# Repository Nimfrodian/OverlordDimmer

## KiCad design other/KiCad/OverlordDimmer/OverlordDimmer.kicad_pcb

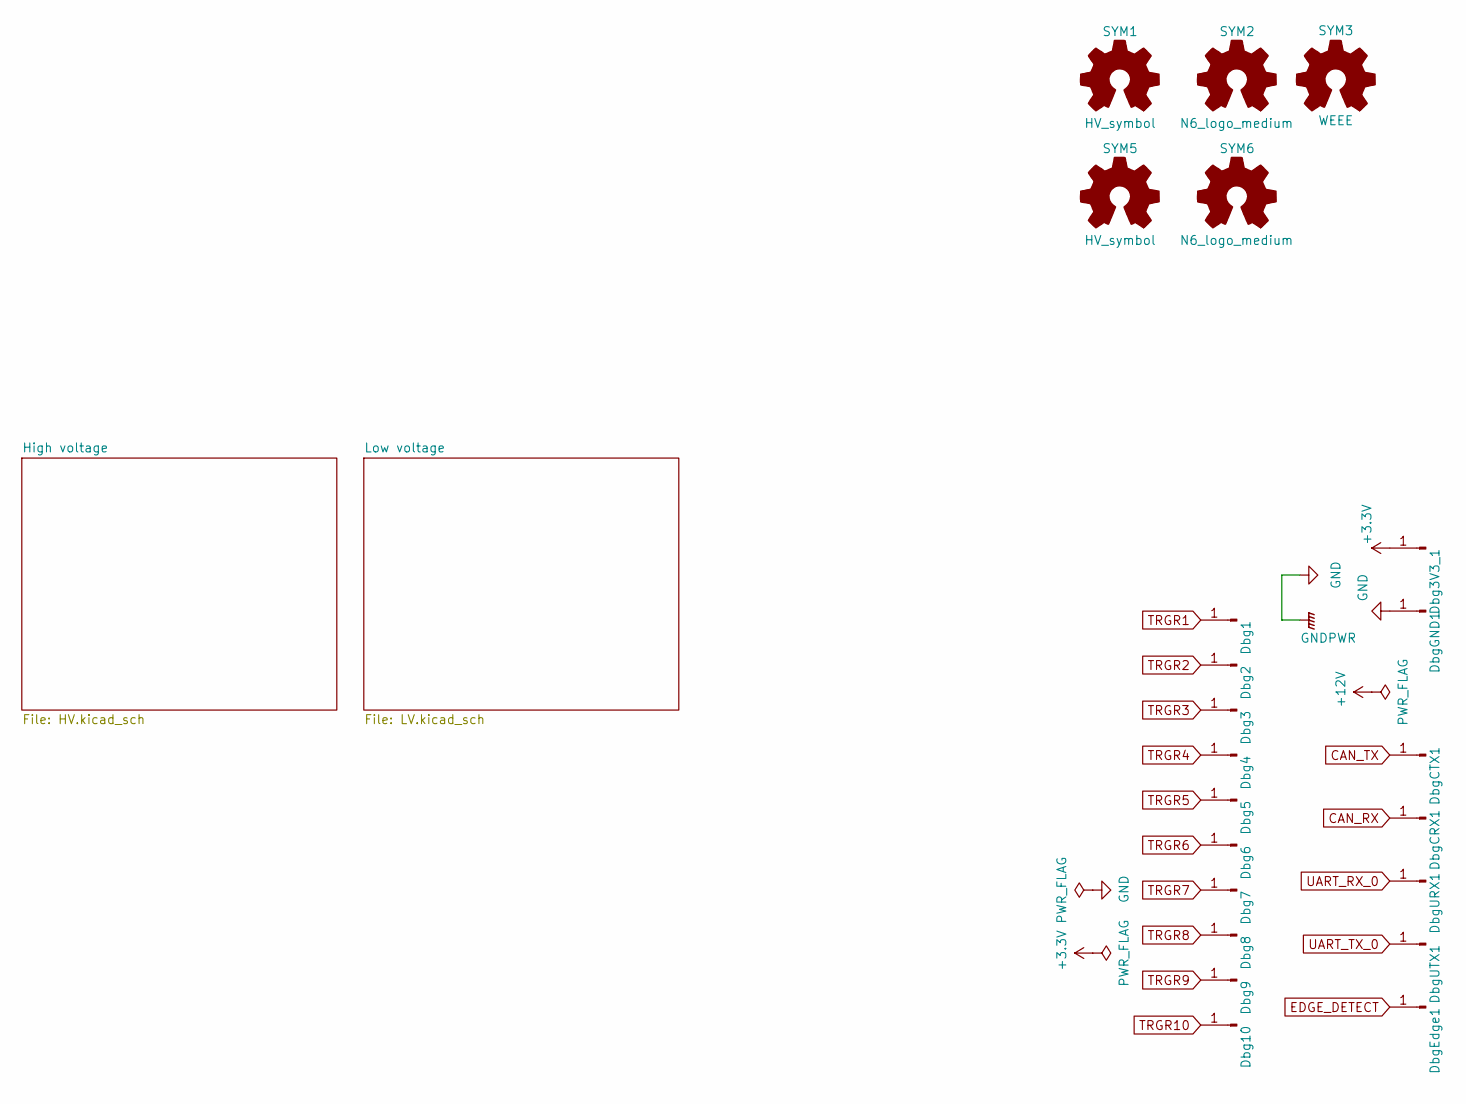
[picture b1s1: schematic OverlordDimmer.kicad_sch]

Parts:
Dbg1, Dbg2, Dbg3, Dbg3V3_1, Dbg4, Dbg5, Dbg6, Dbg7, Dbg8, Dbg9, Dbg10: Connector_Conn_01x01_Male; PinHeader_1x01_P2.54mm_Vertical
DbgCRX1: Connector_Conn_01x01_Male; PinHeader_1x01_P2.54mm_Vertical
DbgCTX1: Connector_Conn_01x01_Male; PinHeader_1x01_P2.54mm_Vertical
DbgEdge1: Connector_Conn_01x01_Male; PinHeader_1x01_P2.54mm_Vertical
DbgGND1: Connector_Conn_01x01_Male; PinHeader_1x01_P2.54mm_Vertical
DbgURX1: Connector_Conn_01x01_Male; PinHeader_1x01_P2.54mm_Vertical
DbgUTX1: Connector_Conn_01x01_Male; PinHeader_1x01_P2.54mm_Vertical
SYM1, SYM5: HV_symbol
SYM2, SYM6: N6_logo_medium; Symbol_N6Industries_medium
SYM3: WEEE; WEEE-Logo_5.6x8mm_SilkScreen

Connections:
+3.3V: Dbg3V3_1.1; also elsewhere on the board
CAN_RX: DbgCRX1.1; also elsewhere on the board
CAN_TX: DbgCTX1.1; also elsewhere on the board
EDGE_DETECT: DbgEdge1.1; also elsewhere on the board
GND: DbgGND1.1; also elsewhere on the board
TRGR1: Dbg1.1; also elsewhere on the board
TRGR2: Dbg2.1; also elsewhere on the board
TRGR3: Dbg3.1; also elsewhere on the board
TRGR4: Dbg4.1; also elsewhere on the board
TRGR5: Dbg5.1; also elsewhere on the board
TRGR6: Dbg6.1; also elsewhere on the board
TRGR7: Dbg7.1; also elsewhere on the board
TRGR8: Dbg8.1; also elsewhere on the board
TRGR9: Dbg9.1; also elsewhere on the board
TRGR10: Dbg10.1; also elsewhere on the board
UART_RX_0: DbgURX1.1; also elsewhere on the board
UART_TX_0: DbgUTX1.1; also elsewhere on the board

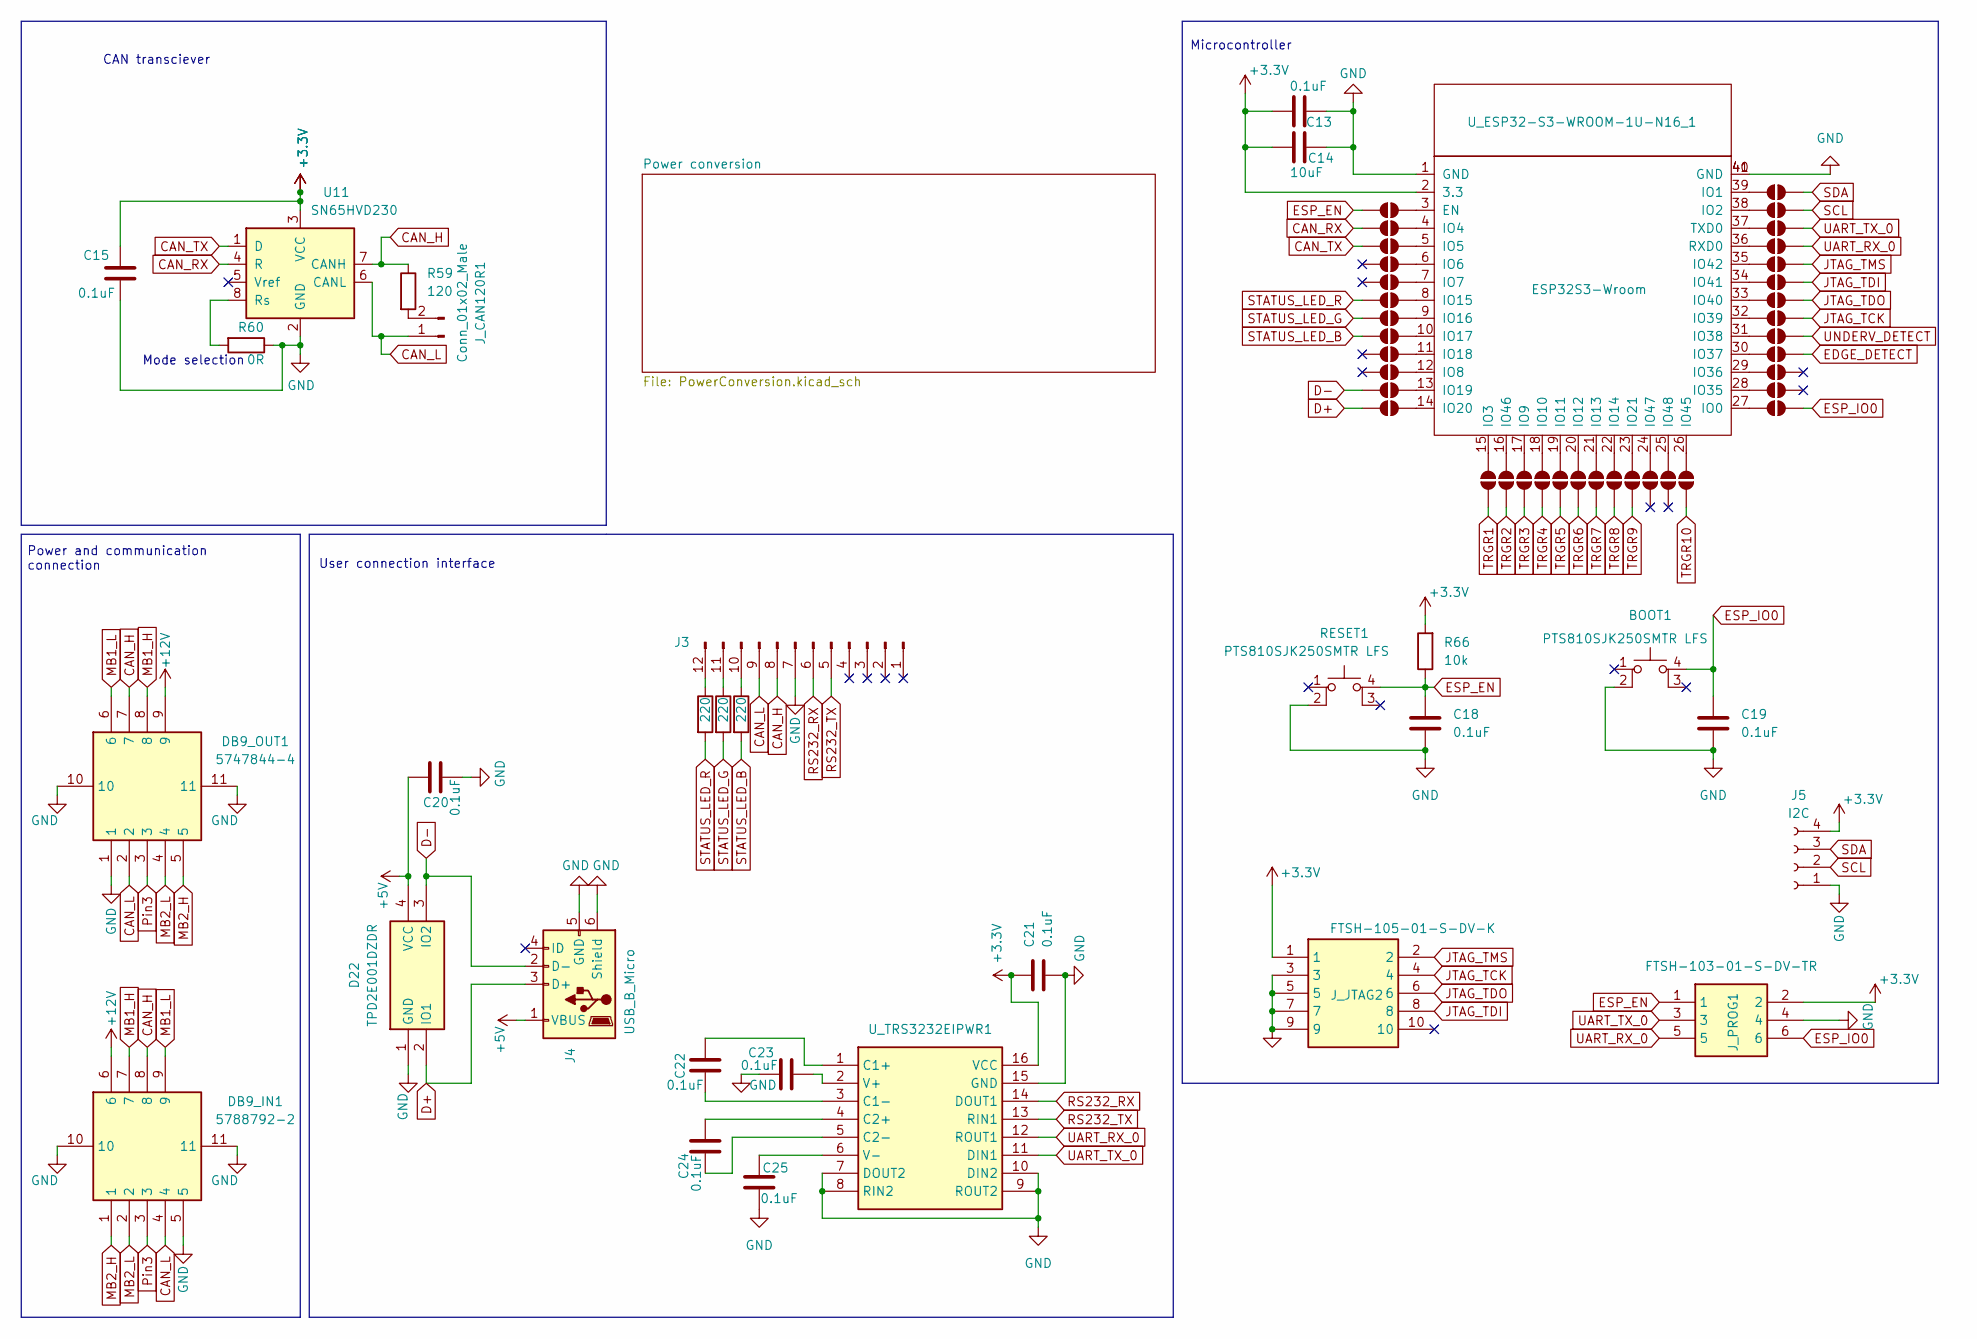
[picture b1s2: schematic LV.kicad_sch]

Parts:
BOOT1: PTS810SJK250SMTR LFS; PTS810SJK250SMTRLFS
C13, C15, C18, C19, C20, C21, C22, C23, C24, C25: 0.1uF; C_0805_2012Metric_Pad1.18x1.45mm_HandSolder
C14: 10uF; C_0805_2012Metric_Pad1.18x1.45mm_HandSolder
D22: TPD2E001DZDR; Mouser Part Number 595-TPD2E001DZDR
DB9_IN1: 5788792-2; 5788792; Mouser Part Number 571-5747844-4
DB9_OUT1: 5747844-4; 57478444; Mouser Part Number 571-5747844-4
J3: Conn_01x12_Pin; Molex_Picoflex_90325-0012_2x06_P1.27mm_Vertical
J4: USB_B_Micro; USB_Micro-B_Wuerth_614105150721_Vertical_CircularHoles
J5: I2C; PinHeader_1x04_P1.27mm_Vertical
JP1, JP2, JP3, JP4, JP5, JP6, JP7, JP8, JP9, JP10, JP11, JP12, JP13, JP14, JP15, JP16, JP17, JP18, JP19, JP20, JP21, JP22, JP23, JP24, JP25, JP26, JP27, JP28, JP29, JP30, JP31, JP32, JP33, JP34, JP35, JP36, JP37: SolderJumper_2_Open; SolderJumper-2_P1.3mm_Open_RoundedPad1.0x1.5mm
J_CAN120R1: Conn_01x02_Male; PinHeader_1x02_P2.54mm_Vertical
J_JTAG2: FTSH-105-01-S-DV-K; FTSH-105-XX-YYY-DV-K; Mouser Part Number 200-FTSH10501SDVK
J_PROG1: FTSH-103-01-S-DV-TR; FTSH-103-XX-YYY-DV-TR; Mouser Part Number 200-FTSH10301SDVTR
R59: 120; R_0805_2012Metric_Pad1.20x1.40mm_HandSolder
R60: 0R; R_0805_2012Metric_Pad1.20x1.40mm_HandSolder
R63, R64, R65: 220; R_0805_2012Metric_Pad1.20x1.40mm_HandSolder
R66: 10k; R_0805_2012Metric_Pad1.20x1.40mm_HandSolder
RESET1: PTS810SJK250SMTR LFS; PTS810SJK250SMTRLFS
U11: SN65HVD230; SOIC-8_3.9x4.9mm_P1.27mm
U_ESP32-S3-WROOM-1U-N16_1: ESP32S3-Wroom; ESP32-S3-WROOM-1U
U_TRS3232EIPWR1: TRS3232EIPWR; SOP65P640X120-16N; Mouser Part Number 595-TRS3232EIPWR

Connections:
+3.3V: C13.1, C14.1, C15.1, C21.1, J5.4, J_JTAG2.1, J_PROG1.2, R66.2, U11.3 (VCC), U_ESP32-S3-WROOM-1U-N16_1.2 (3.3), U_TRS3232EIPWR1.16 (VCC); also elsewhere on the board
+5V: C20.1, D22.4 (VCC), J4.1 (VBUS); also elsewhere on the board
+12V: DB9_IN1.6, DB9_OUT1.9; also elsewhere on the board
CAN_H: DB9_IN1.8, DB9_OUT1.7, J3.8, R59.1, U11.7 (CANH)
CAN_L: DB9_IN1.4, DB9_OUT1.2, J3.9, J_CAN120R1.1, U11.6 (CANL)
CAN_RX: JP4.2 (B), U11.4 (R); also elsewhere on the board
CAN_TX: JP6.2 (B), U11.1 (D); also elsewhere on the board
D+: D22.2 (IO1), J4.3 (D+), JP24.2 (B)
D-: D22.3 (IO2), J4.2 (D-), JP22.2 (B)
EDGE_DETECT: JP19.2 (B); also elsewhere on the board
ESP_EN: C18.1, JP2.2 (B), J_PROG1.1, R66.1, RESET1.4 (A)
ESP_IO0: BOOT1.4 (A), C19.1, JP25.2 (B), J_PROG1.6
GND: BOOT1.2, C13.2, C14.2, C15.2, C18.2, C19.2, C20.2, C21.2, C23.1, C25.1, D22.1 (GND), DB9_IN1.5, DB9_IN1.10, DB9_IN1.11, DB9_OUT1.1, DB9_OUT1.10, DB9_OUT1.11, J3.7, J4.5 (GND), J4.6 (Shield), J5.1, J_JTAG2.3, J_JTAG2.5, J_JTAG2.7, J_JTAG2.9, J_PROG1.4, R60.1, RESET1.2, U11.2 (GND), U_ESP32-S3-WROOM-1U-N16_1.1 (GND), U_ESP32-S3-WROOM-1U-N16_1.40 (GND), U_ESP32-S3-WROOM-1U-N16_1.41 (GND), U_TRS3232EIPWR1.7 (DOUT2), U_TRS3232EIPWR1.8 (RIN2), U_TRS3232EIPWR1.9 (ROUT2), U_TRS3232EIPWR1.10 (DIN2), U_TRS3232EIPWR1.15 (GND); also elsewhere on the board
JTAG_TCK: JP15.2 (B), J_JTAG2.4
JTAG_TDI: JP11.2 (B), J_JTAG2.8
JTAG_TDO: JP13.2 (B), J_JTAG2.6
JTAG_TMS: JP9.2 (B), J_JTAG2.2
MB1_H: DB9_IN1.7, DB9_OUT1.8
MB1_L: DB9_IN1.9, DB9_OUT1.6
MB2_H: DB9_IN1.1, DB9_OUT1.5
MB2_L: DB9_IN1.2, DB9_OUT1.4
unnamed: J3.10, R65.1
unnamed: J3.11, R64.1
unnamed: J3.12, R63.1
unnamed: JP1.1 (A), U_ESP32-S3-WROOM-1U-N16_1.39 (IO1)
unnamed: JP2.1 (A), U_ESP32-S3-WROOM-1U-N16_1.3 (EN)
unnamed: JP3.1 (A), U_ESP32-S3-WROOM-1U-N16_1.38 (IO2)
unnamed: JP4.1 (A), U_ESP32-S3-WROOM-1U-N16_1.4 (IO4)
unnamed: JP5.1 (A), U_ESP32-S3-WROOM-1U-N16_1.37 (TXD0)
unnamed: JP6.1 (A), U_ESP32-S3-WROOM-1U-N16_1.5 (IO5)
unnamed: JP7.1 (A), U_ESP32-S3-WROOM-1U-N16_1.36 (RXD0)
unnamed: JP8.1 (A), U_ESP32-S3-WROOM-1U-N16_1.6 (IO6)
unnamed: JP9.1 (A), U_ESP32-S3-WROOM-1U-N16_1.35 (IO42)
unnamed: JP10.1 (A), U_ESP32-S3-WROOM-1U-N16_1.7 (IO7)
unnamed: JP11.1 (A), U_ESP32-S3-WROOM-1U-N16_1.34 (IO41)
unnamed: JP12.1 (A), U_ESP32-S3-WROOM-1U-N16_1.8 (IO15)
unnamed: JP13.1 (A), U_ESP32-S3-WROOM-1U-N16_1.33 (IO40)
unnamed: JP14.1 (A), U_ESP32-S3-WROOM-1U-N16_1.9 (IO16)
unnamed: JP15.1 (A), U_ESP32-S3-WROOM-1U-N16_1.32 (IO39)
unnamed: JP16.1 (A), U_ESP32-S3-WROOM-1U-N16_1.10 (IO17)
unnamed: JP17.1 (A), U_ESP32-S3-WROOM-1U-N16_1.31 (IO38)
unnamed: JP18.1 (A), U_ESP32-S3-WROOM-1U-N16_1.11 (IO18)
unnamed: JP19.1 (A), U_ESP32-S3-WROOM-1U-N16_1.30 (IO37)
unnamed: JP20.1 (A), U_ESP32-S3-WROOM-1U-N16_1.12 (IO8)
unnamed: JP21.1 (A), U_ESP32-S3-WROOM-1U-N16_1.29 (IO36)
unnamed: JP22.1 (A), U_ESP32-S3-WROOM-1U-N16_1.13 (IO19)
unnamed: JP23.1 (A), U_ESP32-S3-WROOM-1U-N16_1.28 (IO35)
unnamed: JP24.1 (A), U_ESP32-S3-WROOM-1U-N16_1.14 (IO20)
unnamed: JP25.1 (A), U_ESP32-S3-WROOM-1U-N16_1.27 (IO0)
unnamed: JP26.1 (A), U_ESP32-S3-WROOM-1U-N16_1.15 (IO3)
unnamed: JP27.1 (A), U_ESP32-S3-WROOM-1U-N16_1.16 (IO46)
unnamed: JP28.1 (A), U_ESP32-S3-WROOM-1U-N16_1.17 (IO9)
unnamed: JP29.1 (A), U_ESP32-S3-WROOM-1U-N16_1.18 (IO10)
unnamed: JP30.1 (A), U_ESP32-S3-WROOM-1U-N16_1.19 (IO11)
unnamed: JP31.1 (A), U_ESP32-S3-WROOM-1U-N16_1.20 (IO12)
unnamed: JP32.1 (A), U_ESP32-S3-WROOM-1U-N16_1.21 (IO13)
unnamed: JP33.1 (A), U_ESP32-S3-WROOM-1U-N16_1.22 (IO14)
unnamed: JP34.1 (A), U_ESP32-S3-WROOM-1U-N16_1.23 (IO21)
unnamed: JP35.1 (A), U_ESP32-S3-WROOM-1U-N16_1.24 (IO47)
unnamed: JP36.1 (A), U_ESP32-S3-WROOM-1U-N16_1.25 (IO48)
unnamed: JP37.1 (A), U_ESP32-S3-WROOM-1U-N16_1.26 (IO45)
unnamed: J_CAN120R1.2, R59.2
unnamed: R60.2, U11.8 (Rs)
unnamed: C22.1, U_TRS3232EIPWR1.1 (C1+)
unnamed: C22.2, U_TRS3232EIPWR1.3 (C1-)
unnamed: C24.2, U_TRS3232EIPWR1.4 (C2+)
unnamed: C24.1, U_TRS3232EIPWR1.5 (C2-)
unnamed: C23.2, U_TRS3232EIPWR1.2 (V+)
unnamed: C25.2, U_TRS3232EIPWR1.6 (V-)
Pin3: DB9_IN1.3, DB9_OUT1.3
RS232_RX: J3.6, U_TRS3232EIPWR1.14 (DOUT1)
RS232_TX: J3.5, U_TRS3232EIPWR1.13 (RIN1)
SCL: J5.2, JP3.2 (B); also elsewhere on the board
SDA: J5.3, JP1.2 (B); also elsewhere on the board
STATUS_LED_B: JP16.2 (B), R65.2
STATUS_LED_G: JP14.2 (B), R64.2
STATUS_LED_R: JP12.2 (B), R63.2
TRGR1: JP26.2 (B); also elsewhere on the board
TRGR2: JP27.2 (B); also elsewhere on the board
TRGR3: JP28.2 (B); also elsewhere on the board
TRGR4: JP29.2 (B); also elsewhere on the board
TRGR5: JP30.2 (B); also elsewhere on the board
TRGR6: JP31.2 (B); also elsewhere on the board
TRGR7: JP32.2 (B); also elsewhere on the board
TRGR8: JP33.2 (B); also elsewhere on the board
TRGR9: JP34.2 (B); also elsewhere on the board
TRGR10: JP37.2 (B); also elsewhere on the board
UART_RX_0: JP7.2 (B), J_PROG1.5, U_TRS3232EIPWR1.12 (ROUT1); also elsewhere on the board
UART_TX_0: JP5.2 (B), J_PROG1.3, U_TRS3232EIPWR1.11 (DIN1); also elsewhere on the board
UNDERV_DETECT: JP17.2 (B); also elsewhere on the board

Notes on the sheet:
Power and communication connection
Microcontroller
Mode selection
CAN transciever
User connection interface

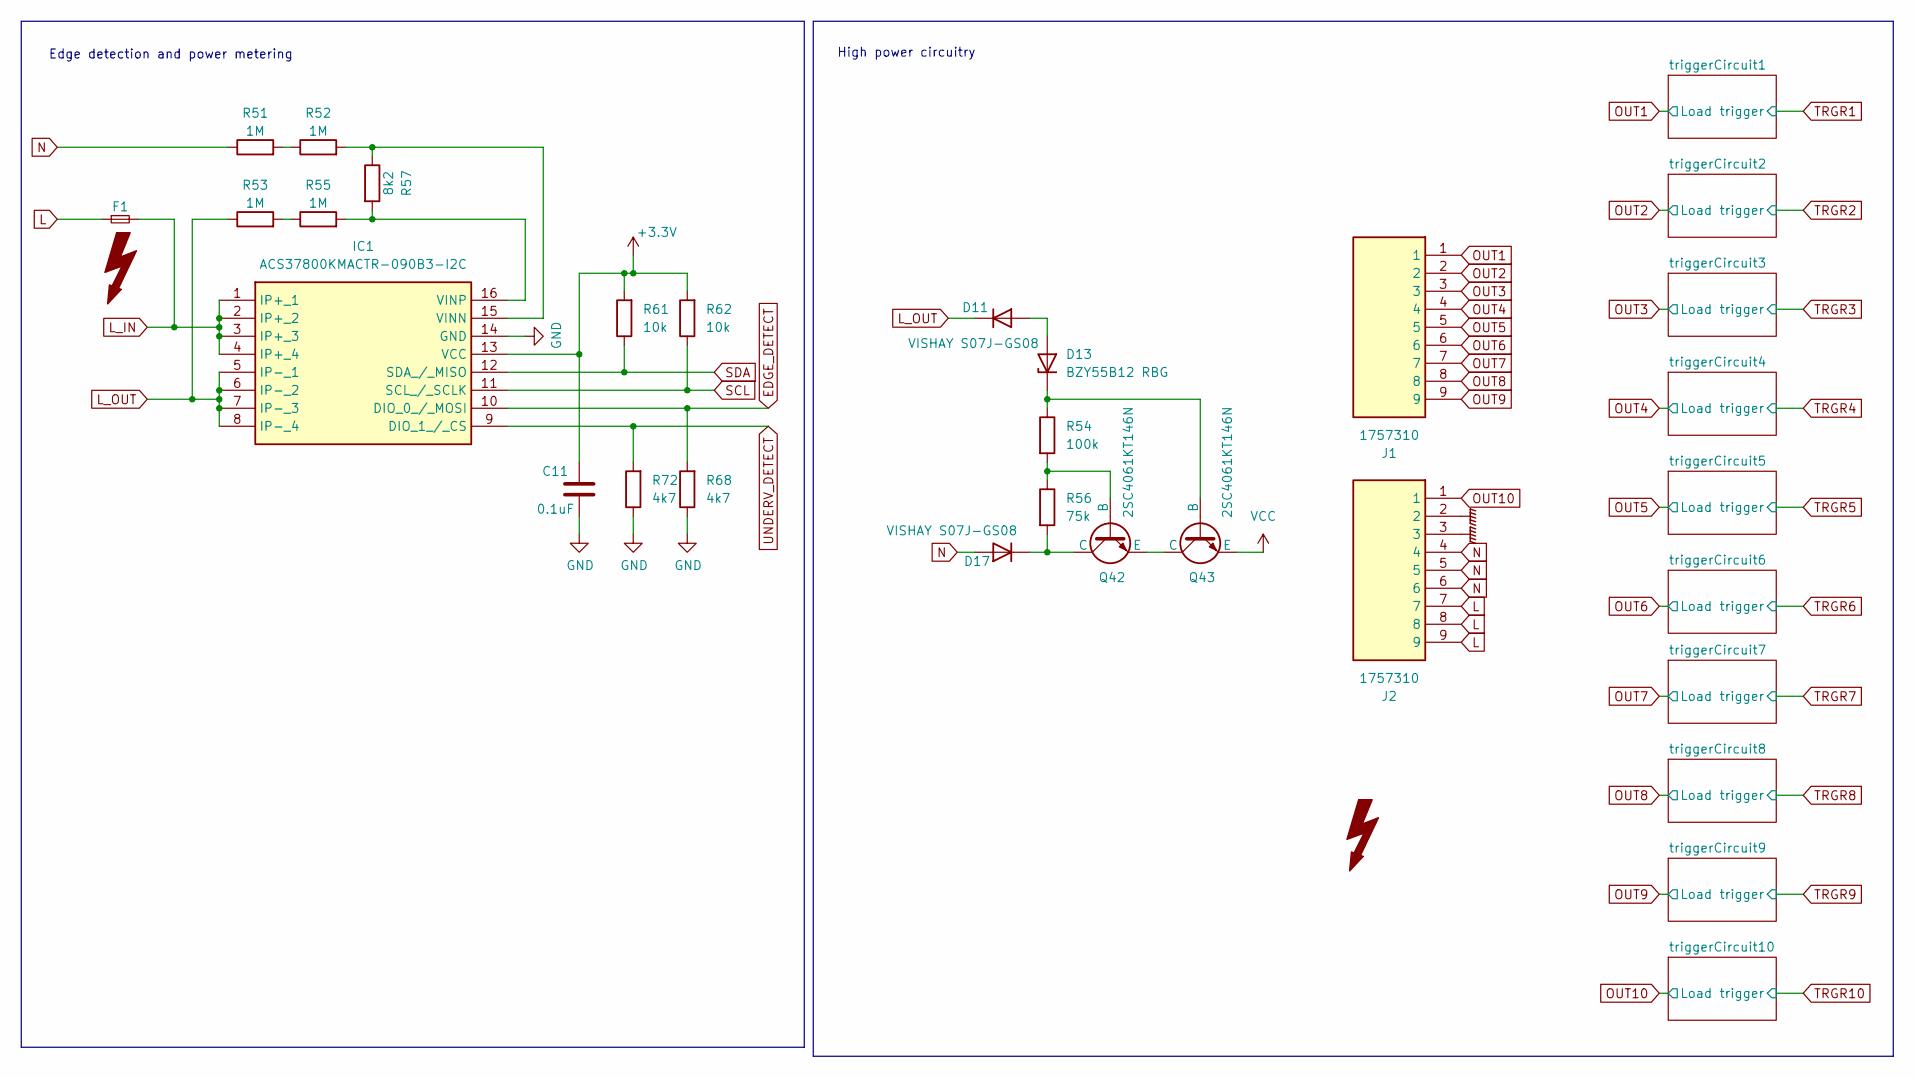
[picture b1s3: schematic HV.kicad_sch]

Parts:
C11: 0.1uF; C_0805_2012Metric_Pad1.18x1.45mm_HandSolder
D11, D17: VISHAY S07J-GS08; D_SMF
D13: BZY55B12 RBG; D_0805_2012Metric_Pad1.15x1.40mm_HandSolder
F1: Fuse_Small; Fuseholder_Clip-5x20mm_Bel_FC-203-22_Lateral_P17.80x5.00mm_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
IC1: ACS37800KMACTR-090B3-I2C; SOIC127P1030X265-16N; Mouser Part Number 250-KMACTR-090B3-I2C
J1, J2: 1757310; Mouser Part Number 651-1757310
Q42, Q43: 2SC4061KT146N; SC-59_Handsoldering
R51, R52, R53, R55: 1M; R_0805_2012Metric_Pad1.20x1.40mm_HandSolder
R54: 100k; R_0805_2012Metric_Pad1.20x1.40mm_HandSolder
R56: 75k; R_0805_2012Metric_Pad1.20x1.40mm_HandSolder
R57: 8k2; R_0805_2012Metric_Pad1.20x1.40mm_HandSolder
R61, R62: 10k; R_0805_2012Metric_Pad1.20x1.40mm_HandSolder
R68, R72: 4k7; R_0805_2012Metric_Pad1.20x1.40mm_HandSolder

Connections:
+3.3V: C11.1, IC1.13 (VCC), R61.2, R62.2; also elsewhere on the board
EDGE_DETECT: IC1.10 (DIO_0_/_MOSI), R68.2; also elsewhere on the board
GND: C11.2, IC1.14 (GND), J2.2, J2.3, R68.1, R72.1; also elsewhere on the board
L: F1.1, J2.7, J2.8, J2.9
L_IN: F1.2, IC1.1 (IP+_1), IC1.2 (IP+_2), IC1.3 (IP+_3), IC1.4 (IP+_4)
L_OUT: D11.1 (K), IC1.5 (IP-_1), IC1.6 (IP-_2), IC1.7 (IP-_3), IC1.8 (IP-_4), R53.1; also elsewhere on the board
N: D17.2 (A), J2.4, J2.5, J2.6, R51.1
unnamed: D11.2 (A), D13.2 (A)
unnamed: D13.1 (K), Q43.1 (B), R54.1
unnamed: D17.1 (K), Q42.3 (C), R56.2
unnamed: IC1.15 (VINN), R52.2, R57.1
unnamed: IC1.16 (VINP), R55.2, R57.2
unnamed: Q42.1 (B), R54.2, R56.1
unnamed: Q42.2 (E), Q43.3 (C)
unnamed: R51.2, R52.1
unnamed: R53.2, R55.1
OUT1: J1.1; also elsewhere on the board
OUT2: J1.2; also elsewhere on the board
OUT3: J1.3; also elsewhere on the board
OUT4: J1.4; also elsewhere on the board
OUT5: J1.5; also elsewhere on the board
OUT6: J1.6; also elsewhere on the board
OUT7: J1.7; also elsewhere on the board
OUT8: J1.8; also elsewhere on the board
OUT9: J1.9; also elsewhere on the board
OUT10: J2.1; also elsewhere on the board
SCL: IC1.11 (SCL_/_SCLK), R62.1; also elsewhere on the board
SDA: IC1.12 (SDA_/_MISO), R61.1; also elsewhere on the board
UNDERV_DETECT: IC1.9 (DIO_1_/_CS), R72.2; also elsewhere on the board
VCC: Q43.2 (E); also elsewhere on the board

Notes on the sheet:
Edge detection and power metering
High power circuitry

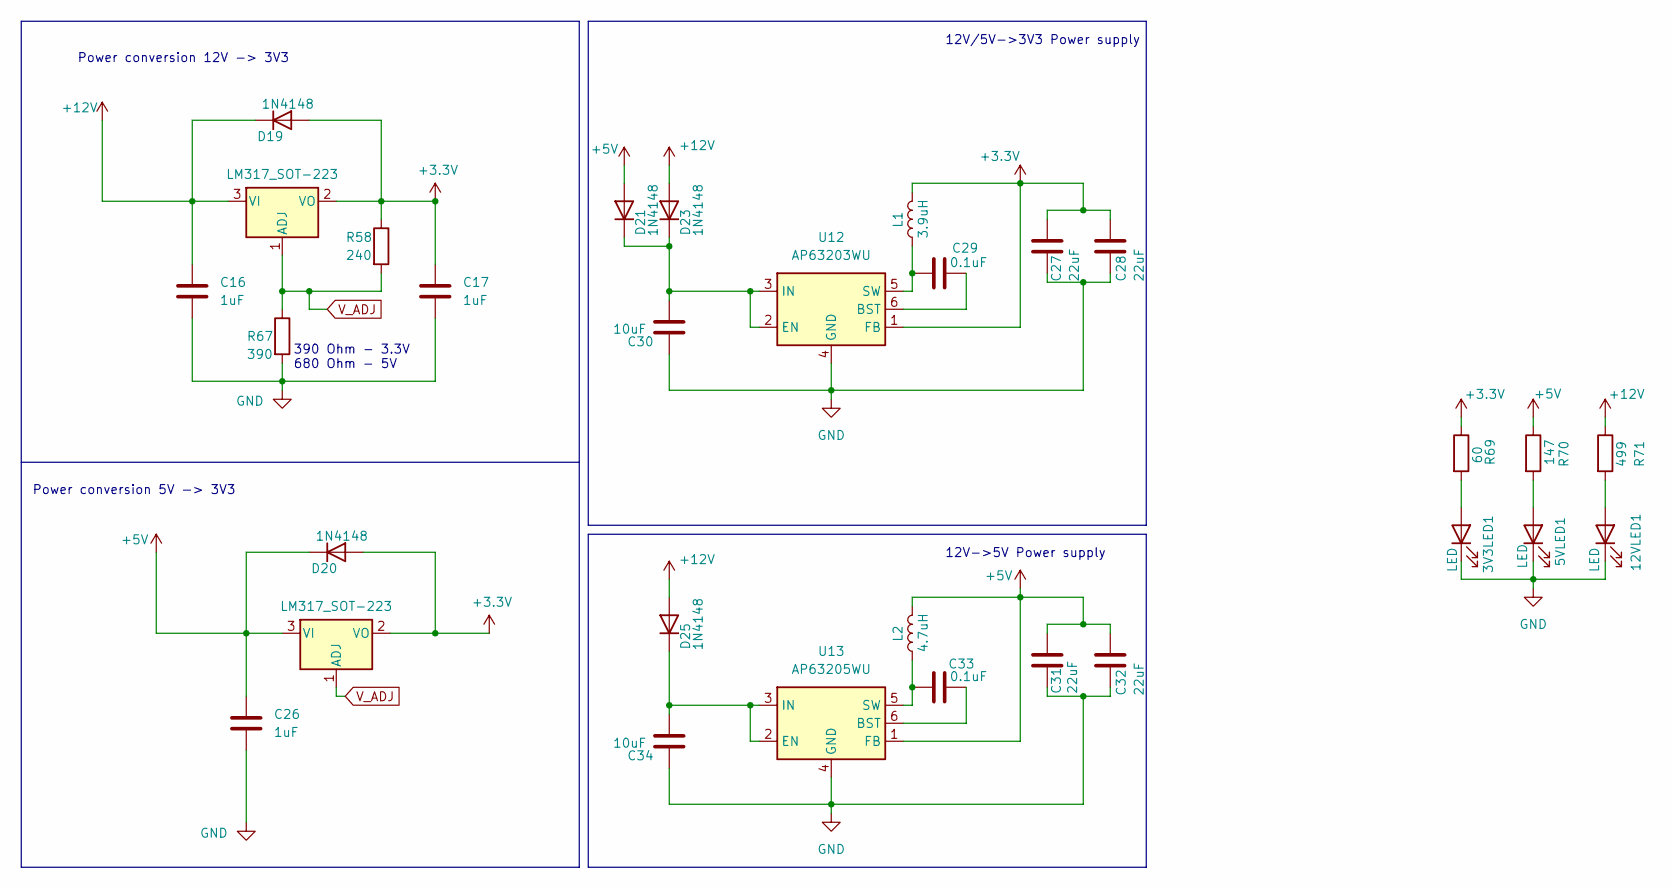
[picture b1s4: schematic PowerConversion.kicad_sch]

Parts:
3V3LED1, 5VLED1, 12VLED1: LED; LED_0805_2012Metric_Pad1.15x1.40mm_HandSolder
C16, C17, C26: 1uF; C_0805_2012Metric_Pad1.18x1.45mm_HandSolder
C27, C28, C31, C32: 22uF; C_0805_2012Metric_Pad1.18x1.45mm_HandSolder
C29, C33: 0.1uF; C_0805_2012Metric_Pad1.18x1.45mm_HandSolder
C30, C34: 10uF; C_0805_2012Metric_Pad1.18x1.45mm_HandSolder
D19, D20, D21, D23, D25: 1N4148; D_0805_2012Metric_Pad1.15x1.40mm_HandSolder
L1: 3.9uH; L_Bourns_SDR0604
L2: 4.7uH; L_Bourns_SDR0604
R58: 240; R_0805_2012Metric
R67: 390; R_0805_2012Metric
R69: 60; R_0805_2012Metric_Pad1.20x1.40mm_HandSolder
R70: 147; R_0805_2012Metric_Pad1.20x1.40mm_HandSolder
R71: 499; R_0805_2012Metric_Pad1.20x1.40mm_HandSolder
U12: AP63203WU; TSOT-23-6
U13: AP63205WU; TSOT-23-6
U_LM317_1, U_LM317_2: LM317_SOT-223; SOT-223-3_TabPin2

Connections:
+3.3V: C17.1, C27.1, C28.1, D19.2 (A), D20.2 (A), L1.2, R58.1, R69.1, U12.1 (FB), U_LM317_1.2 (VO), U_LM317_2.2 (VO); also elsewhere on the board
+5V: C26.1, C31.1, C32.1, D20.1 (K), D21.2 (A), L2.2, R70.1, U13.1 (FB), U_LM317_2.3 (VI); also elsewhere on the board
+12V: C16.1, D19.1 (K), D23.2 (A), D25.2 (A), R71.1, U_LM317_1.3 (VI); also elsewhere on the board
GND: 3V3LED1.1 (K), 5VLED1.1 (K), 12VLED1.1 (K), C16.2, C17.2, C26.2, C27.2, C28.2, C30.1, C31.2, C32.2, C34.1, R67.2, U12.4 (GND), U13.4 (GND); also elsewhere on the board
unnamed: 3V3LED1.2 (A), R69.2
unnamed: 5VLED1.2 (A), R70.2
unnamed: 12VLED1.2 (A), R71.2
unnamed: C30.2, D21.1 (K), D23.1 (K), U12.2 (EN), U12.3 (IN)
unnamed: C34.2, D25.1 (K), U13.2 (EN), U13.3 (IN)
unnamed: C29.2, U12.6 (BST)
unnamed: C29.1, L1.1, U12.5 (SW)
unnamed: C33.2, U13.6 (BST)
unnamed: C33.1, L2.1, U13.5 (SW)
V_ADJ: R58.2, R67.1, U_LM317_1.1 (ADJ), U_LM317_2.1 (ADJ)

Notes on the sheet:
390 Ohm - 3.3V 680 Ohm - 5V
12V->5V Power supply
12V/5V->3V3 Power supply
Power conversion 5V -> 3V3
Power conversion 12V -> 3V3

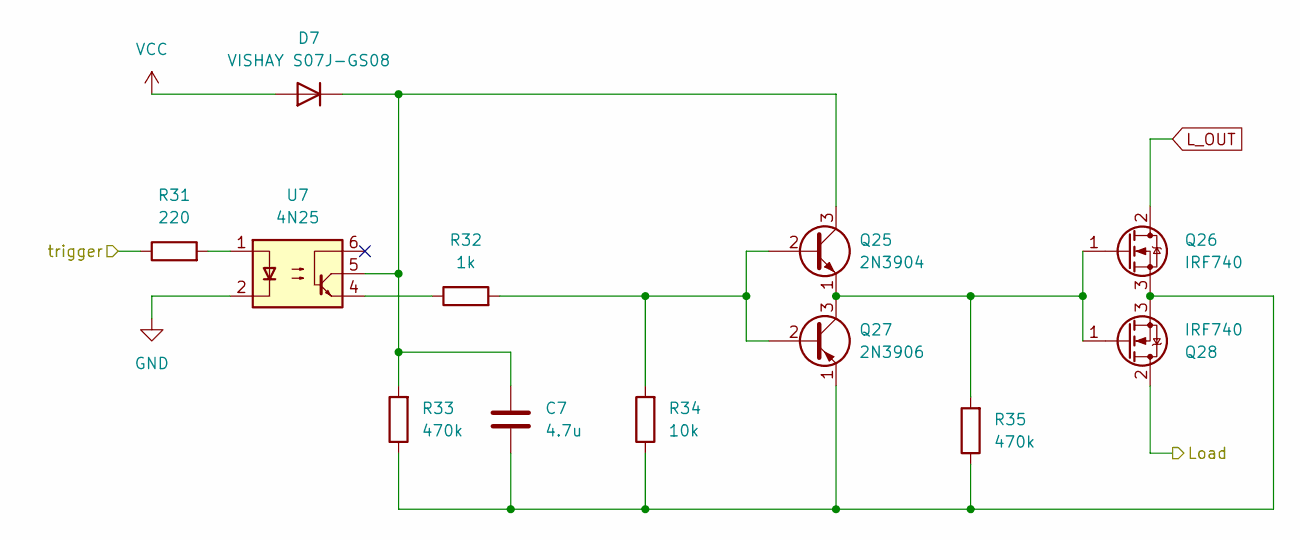
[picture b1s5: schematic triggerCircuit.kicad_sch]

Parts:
C7: 4.7u; C_1210_3225Metric_Pad1.33x2.70mm_HandSolder
D7: VISHAY S07J-GS08; D_SMF
Q25: 2N3904; TO-92_Inline
Q26, Q28: IRF740; TO-220-3_Vertical
Q27: 2N3906; TO-92_Inline
R31: 220; R_0805_2012Metric_Pad1.20x1.40mm_HandSolder
R32: 1k; R_0805_2012Metric_Pad1.20x1.40mm_HandSolder
R33, R35: 470k; R_0805_2012Metric_Pad1.20x1.40mm_HandSolder
R34: 10k; R_0805_2012Metric_Pad1.20x1.40mm_HandSolder
U7: 4N25; DIP-6_W7.62mm

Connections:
GND: U7.2; also elsewhere on the board
L_OUT: Q26.2 (D); also elsewhere on the board
unnamed: C7.1, D7.1 (K), Q25.3 (C), R33.2, U7.5
unnamed: Q25.2 (B), Q27.2 (B), R32.2, R34.2
unnamed: Q25.1 (E), Q26.1 (G), Q27.3 (C), Q28.1 (G), R35.2
unnamed: C7.2, Q26.3 (S), Q27.1 (E), Q28.3 (S), R33.1, R34.1, R35.1
unnamed: R31.2, U7.1
unnamed: R32.1, U7.4
OUT7: Q28.2 (D); also elsewhere on the board
TRGR7: R31.1; also elsewhere on the board
VCC: D7.2 (A); also elsewhere on the board

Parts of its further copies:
C1, C2, C3, C4, C5, C6, C8, C9, C10: 4.7u; C_1210_3225Metric_Pad1.33x2.70mm_HandSolder
D1, D2, D3, D4, D5, D6, D8, D9, D10: VISHAY S07J-GS08; D_SMF
Q1, Q5, Q9, Q13, Q17, Q21, Q29, Q33, Q37: 2N3904; TO-92_Inline
Q2, Q4, Q6, Q8, Q10, Q12, Q14, Q16, Q18, Q20, Q22, Q24, Q30, Q32, Q34, Q36, Q38, Q40: IRF740; TO-220-3_Vertical
Q3, Q7, Q11, Q15, Q19, Q23, Q31, Q35, Q39: 2N3906; TO-92_Inline
R1, R6, R11, R16, R21, R26, R36, R41, R46: 220; R_0805_2012Metric_Pad1.20x1.40mm_HandSolder
R2, R7, R12, R17, R22, R27, R37, R42, R47: 1k; R_0805_2012Metric_Pad1.20x1.40mm_HandSolder
R3, R5, R8, R10, R13, R15, R18, R20, R23, R25, R28, R30, R38, R40, R43, R45, R48, R50: 470k; R_0805_2012Metric_Pad1.20x1.40mm_HandSolder
R4, R9, R14, R19, R24, R29, R39, R44, R49: 10k; R_0805_2012Metric_Pad1.20x1.40mm_HandSolder
U1, U2, U3, U4, U5, U6, U8, U9, U10: 4N25; DIP-6_W7.62mm

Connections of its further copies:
GND: U1.2, U2.2, U3.2, U4.2, U5.2, U6.2, U8.2, U9.2, U10.2; also elsewhere on the board
L_OUT: Q2.2 (D), Q6.2 (D), Q10.2 (D), Q14.2 (D), Q18.2 (D), Q22.2 (D), Q30.2 (D), Q34.2 (D), Q38.2 (D); also elsewhere on the board
unnamed: C1.1, D1.1 (K), Q1.3 (C), R3.2, U1.5
unnamed: C2.1, D2.1 (K), Q5.3 (C), R8.2, U2.5
unnamed: C3.1, D3.1 (K), Q9.3 (C), R13.2, U3.5
unnamed: C4.1, D4.1 (K), Q13.3 (C), R18.2, U4.5
unnamed: C5.1, D5.1 (K), Q17.3 (C), R23.2, U5.5
unnamed: C6.1, D6.1 (K), Q21.3 (C), R28.2, U6.5
unnamed: C8.1, D8.1 (K), Q29.3 (C), R38.2, U8.5
unnamed: C9.1, D9.1 (K), Q33.3 (C), R43.2, U9.5
unnamed: C10.1, D10.1 (K), Q37.3 (C), R48.2, U10.5
unnamed: Q1.2 (B), Q3.2 (B), R2.2, R4.2
unnamed: Q1.1 (E), Q2.1 (G), Q3.3 (C), Q4.1 (G), R5.2
unnamed: C1.2, Q2.3 (S), Q3.1 (E), Q4.3 (S), R3.1, R4.1, R5.1
unnamed: Q5.2 (B), Q7.2 (B), R7.2, R9.2
unnamed: Q5.1 (E), Q6.1 (G), Q7.3 (C), Q8.1 (G), R10.2
unnamed: C2.2, Q6.3 (S), Q7.1 (E), Q8.3 (S), R8.1, R9.1, R10.1
unnamed: Q9.1 (E), Q10.1 (G), Q11.3 (C), Q12.1 (G), R15.2
unnamed: C3.2, Q10.3 (S), Q11.1 (E), Q12.3 (S), R13.1, R14.1, R15.1
unnamed: Q9.2 (B), Q11.2 (B), R12.2, R14.2
unnamed: Q13.2 (B), Q15.2 (B), R17.2, R19.2
unnamed: Q13.1 (E), Q14.1 (G), Q15.3 (C), Q16.1 (G), R20.2
unnamed: C4.2, Q14.3 (S), Q15.1 (E), Q16.3 (S), R18.1, R19.1, R20.1
unnamed: Q17.2 (B), Q19.2 (B), R22.2, R24.2
unnamed: Q17.1 (E), Q18.1 (G), Q19.3 (C), Q20.1 (G), R25.2
unnamed: C5.2, Q18.3 (S), Q19.1 (E), Q20.3 (S), R23.1, R24.1, R25.1
unnamed: Q21.2 (B), Q23.2 (B), R27.2, R29.2
unnamed: Q21.1 (E), Q22.1 (G), Q23.3 (C), Q24.1 (G), R30.2
unnamed: C6.2, Q22.3 (S), Q23.1 (E), Q24.3 (S), R28.1, R29.1, R30.1
unnamed: Q29.2 (B), Q31.2 (B), R37.2, R39.2
unnamed: Q29.1 (E), Q30.1 (G), Q31.3 (C), Q32.1 (G), R40.2
unnamed: C8.2, Q30.3 (S), Q31.1 (E), Q32.3 (S), R38.1, R39.1, R40.1
unnamed: Q33.2 (B), Q35.2 (B), R42.2, R44.2
unnamed: Q33.1 (E), Q34.1 (G), Q35.3 (C), Q36.1 (G), R45.2
unnamed: C9.2, Q34.3 (S), Q35.1 (E), Q36.3 (S), R43.1, R44.1, R45.1
unnamed: Q37.2 (B), Q39.2 (B), R47.2, R49.2
unnamed: Q37.1 (E), Q38.1 (G), Q39.3 (C), Q40.1 (G), R50.2
unnamed: C10.2, Q38.3 (S), Q39.1 (E), Q40.3 (S), R48.1, R49.1, R50.1
unnamed: R1.2, U1.1
unnamed: R2.1, U1.4
unnamed: R6.2, U2.1
unnamed: R7.1, U2.4
unnamed: R11.2, U3.1
unnamed: R12.1, U3.4
unnamed: R16.2, U4.1
unnamed: R17.1, U4.4
unnamed: R21.2, U5.1
unnamed: R22.1, U5.4
unnamed: R26.2, U6.1
unnamed: R27.1, U6.4
unnamed: R36.2, U8.1
unnamed: R37.1, U8.4
unnamed: R41.2, U9.1
unnamed: R42.1, U9.4
unnamed: R46.2, U10.1
unnamed: R47.1, U10.4
OUT1: Q4.2 (D); also elsewhere on the board
OUT2: Q8.2 (D); also elsewhere on the board
OUT3: Q12.2 (D); also elsewhere on the board
OUT4: Q16.2 (D); also elsewhere on the board
OUT5: Q20.2 (D); also elsewhere on the board
OUT6: Q24.2 (D); also elsewhere on the board
OUT8: Q32.2 (D); also elsewhere on the board
OUT9: Q36.2 (D); also elsewhere on the board
OUT10: Q40.2 (D); also elsewhere on the board
TRGR1: R1.1; also elsewhere on the board
TRGR2: R6.1; also elsewhere on the board
TRGR3: R11.1; also elsewhere on the board
TRGR4: R16.1; also elsewhere on the board
TRGR5: R21.1; also elsewhere on the board
TRGR6: R26.1; also elsewhere on the board
TRGR8: R36.1; also elsewhere on the board
TRGR9: R41.1; also elsewhere on the board
TRGR10: R46.1; also elsewhere on the board
VCC: D1.2 (A), D2.2 (A), D3.2 (A), D4.2 (A), D5.2 (A), D6.2 (A), D8.2 (A), D9.2 (A), D10.2 (A); also elsewhere on the board
